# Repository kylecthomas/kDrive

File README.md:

# kDrive
Tactile Remote Control of a Mobile Device  

Project is documented in detail at https://hackaday.io/project/27593-tactile-remote-control-of-a-mobile-device

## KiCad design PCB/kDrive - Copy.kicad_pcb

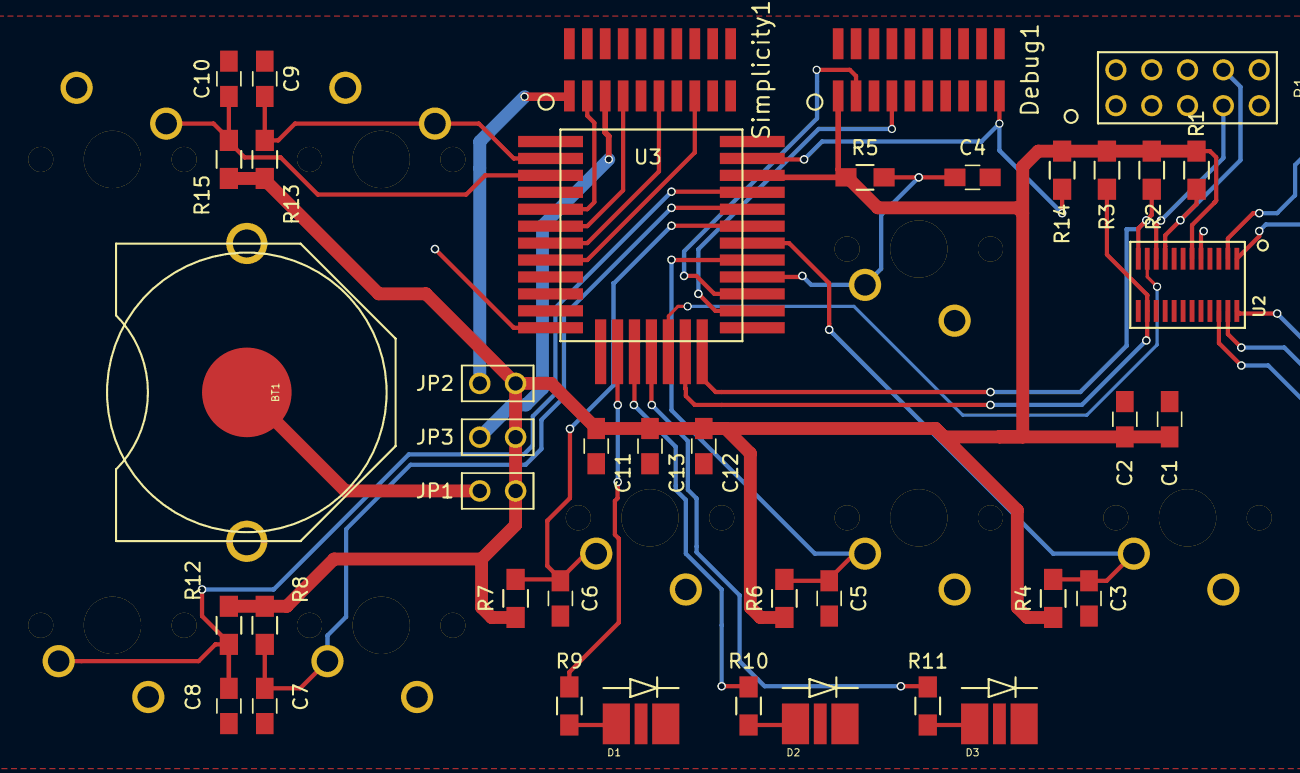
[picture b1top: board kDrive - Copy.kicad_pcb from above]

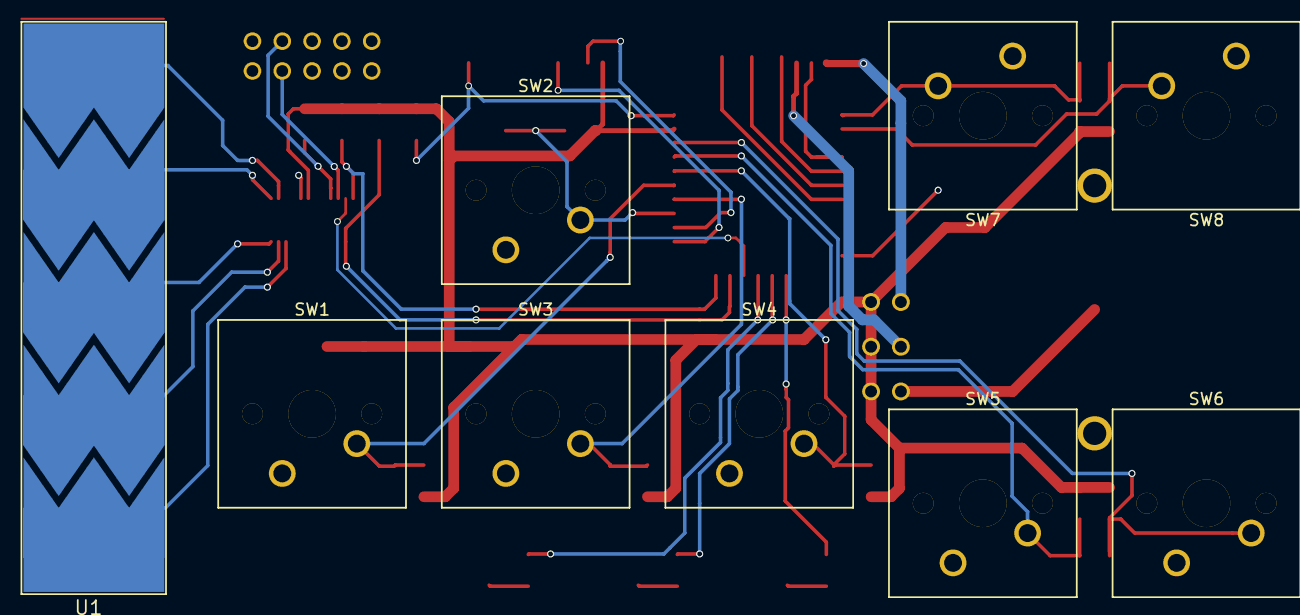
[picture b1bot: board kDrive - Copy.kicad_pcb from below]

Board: 2 copper layers, 49 parts (9 on the bottom side), 36 nets.

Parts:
BT1: Battery; Keystone_3003_CR2032
C1: 0.1u; C_0805_HandSoldering
C2: 4.7u; C_0805_HandSoldering
C3, C4, C5, C6, C7, C8, C9, C10: C; C_0805_HandSoldering
C11, C12: 100n; C_0805_HandSoldering
C13: 10u; C_0805_HandSoldering
D1, D2, D3: LED; LD-CN5M
Debug1: CONN_02X10; GRPB102VWQS-RC
JP1, JP2, JP3: JUMPER; Jumper
P1: CONN_02X05; DIP-5x2_100mil
R1: 1K; R_0805_HandSoldering
R2, R3: 2K; R_0805_HandSoldering
R4, R5, R6, R7, R8, R9, R10, R11, R12, R13, R15: R; R_0805_HandSoldering
R14: 10K; R_0805_HandSoldering
SW1, SW2, SW3, SW4, SW5, SW6, SW7, SW8: SW_PUSH; Cherry_MX1A-C1NW
Simplicity1: CONN_02X10; GRPB102VWQS-RC
U1: Touch_Slider
U2: CPT112S_QSOP; CPT112_TSOP
U3: BGM111

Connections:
/B1: C7.1, R8.2, SW5.1, U3.27
/B2: C8.1, R12.2, SW6.1, U3.28
/B3: C9.1, R13.2, SW7.1, U3.2
/B4: C10.1, R15.2, SW8.1, U3.3
/Bdown: C5.1, R6.2, SW3.1, U3.24
/Bleft: C3.1, R4.2, SW1.1, U3.25
/Bright: C6.1, R7.2, SW4.1, U3.26
/Bup: C4.1, R5.2, SW2.1, U3.23
/CNFG_CLK: P1.7, R1.1, U2.9
/CNFG_DATA: P1.4, U2.10
/I2C_INT: U2.11, U3.17
/I2C_SCL: R2.1, U2.12, U3.19
/I2C_SDA: R3.1, U2.14, U3.18
/LED0: R9.1, U3.14
/LED1: R10.1, U3.15
/LED2: R11.1, U3.16
/RESET: Debug1.10, R14.2, U3.30
/SLIDE_1: U1.1, U2.22
/SLIDE_2: U1.2, U2.23
/SLIDE_3: U1.3, U2.24
/SLIDE_4: U1.4, U2.1
/SLIDE_5: U1.5, U2.2
/SWCLK: Debug1.4, U3.21
/SWDIO: Debug1.2, U3.22
/VCOM_CTS: Simplicity1.6, U3.7
/VCOM_RTS: Simplicity1.8, U3.8
/VCOM_RX: Simplicity1.4, U3.6
/VCOM_TX: Simplicity1.2, U3.5
/VDD3V: JP3.1, Simplicity1.3
/VDD_BGM: C1.2, C2.2, C11.1, C12.1, C13.1, Debug1.1, JP1.2, JP2.2, JP3.2, R1.2, R2.2, R3.2, R4.1, R5.1, R6.1, R7.1, R8.1, R12.1, R13.1, R14.1, R15.1, U2.6, U3.29
/VMCU: JP2.1, Simplicity1.1
GND: BT1.2, C1.1, C2.1, C3.2, C4.2, C5.2, C6.2, C7.2, C8.2, C9.2, C10.2, C11.2, C12.2, C13.2, D1.1, D2.1, D3.1, Debug1.3, Debug1.5, Debug1.15, Debug1.17, Debug1.19, P1.2, P1.3, P1.9, SW1.2, SW2.2, SW3.2, SW4.2, SW5.2, SW6.2, SW7.2, SW8.2, Simplicity1.7, Simplicity1.9, Simplicity1.11, Simplicity1.13, Simplicity1.15, U2.5, U3.1, U3.12, U3.20, U3.31
unnamed: BT1.1, JP1.1
unnamed: D1.2, R9.2
unnamed: D2.2, R10.2
unnamed: D3.2, R11.2

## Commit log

2017-10-24 Create BGM111_firmware
2017-10-24 BGM Firmware
